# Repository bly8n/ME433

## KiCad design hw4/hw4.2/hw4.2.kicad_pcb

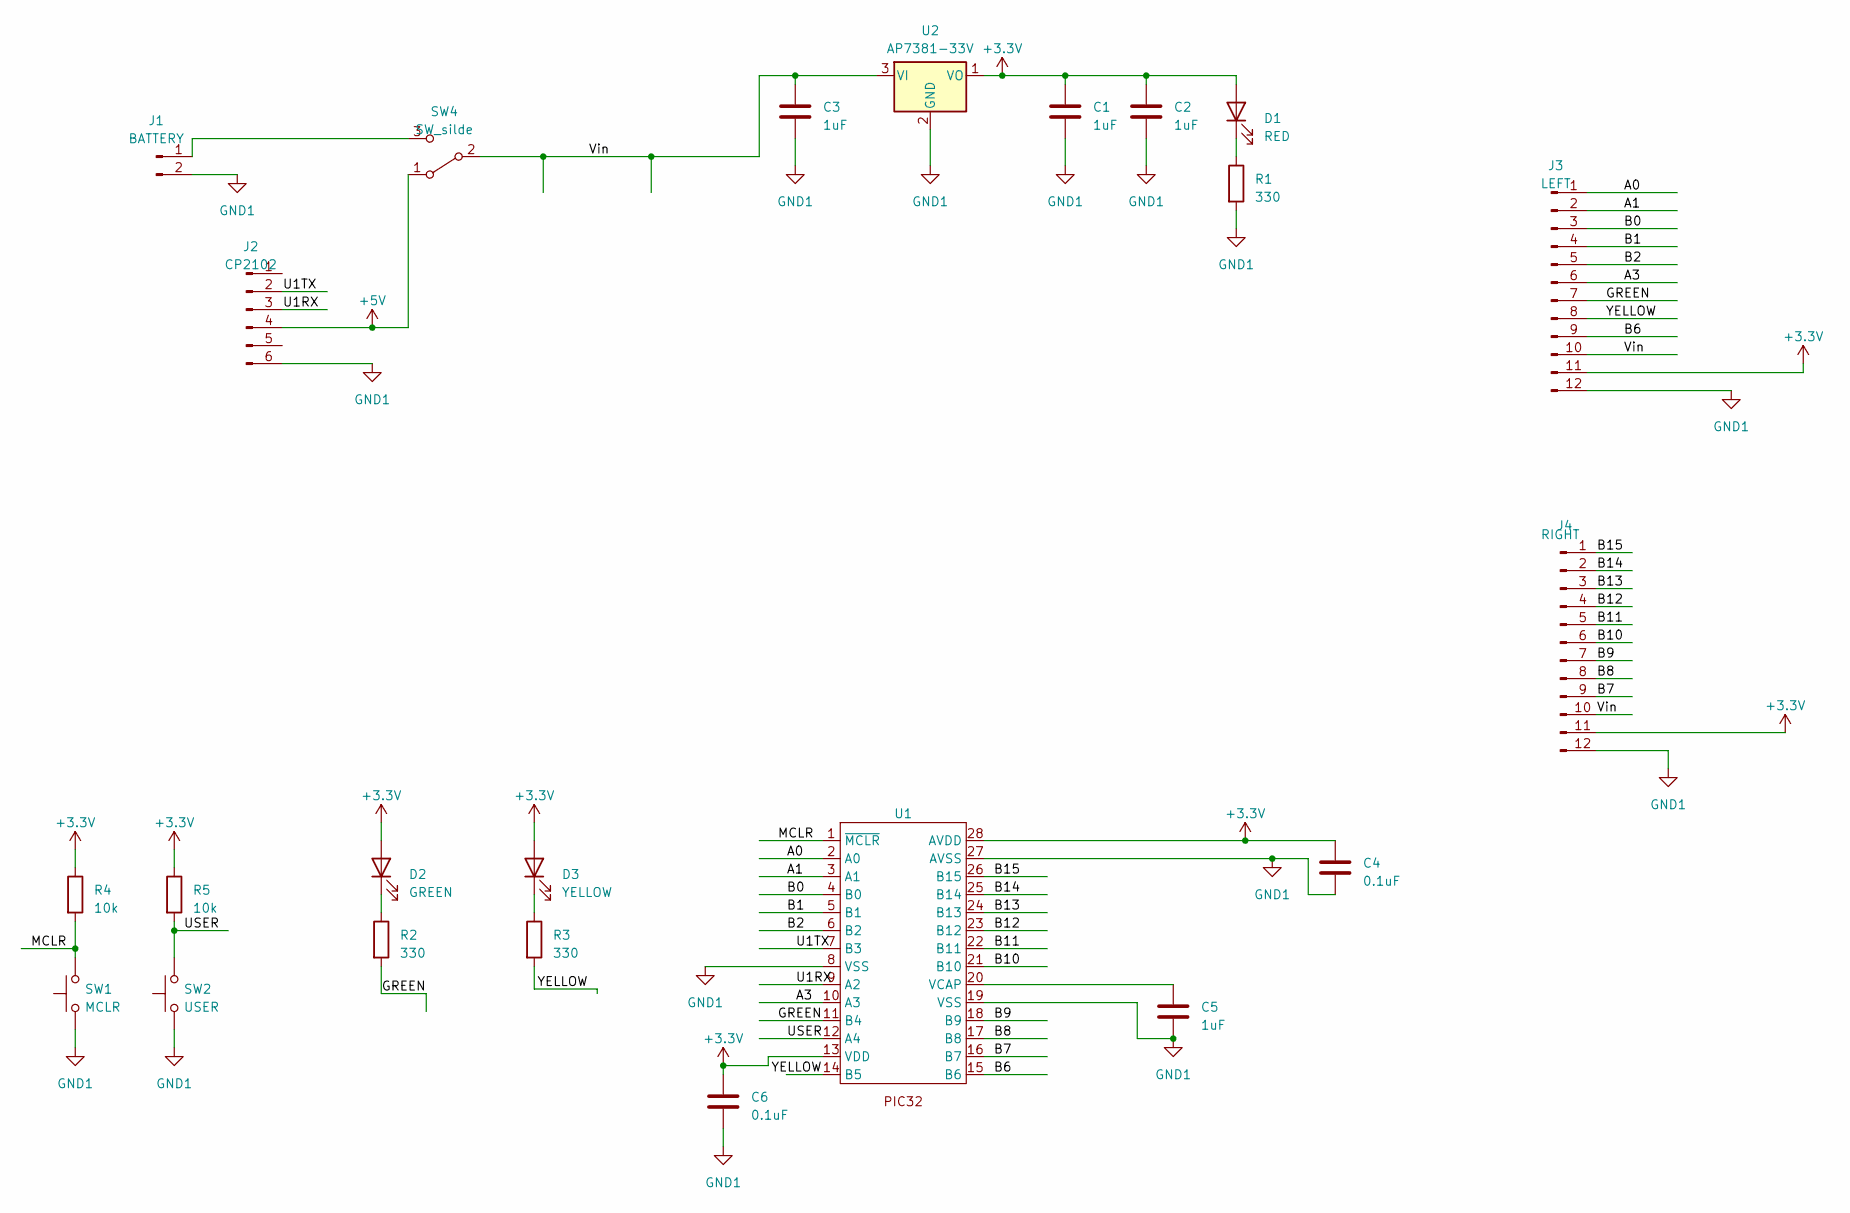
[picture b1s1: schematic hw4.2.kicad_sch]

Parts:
C1, C2, C3, C5: 1uF; C_Disc_D5.1mm_W3.2mm_P5.00mm
C4, C6: 0.1uF; C_Disc_D3.4mm_W2.1mm_P2.50mm
D1: RED; LED_D3.0mm
D2: GREEN; LED_D3.0mm
D3: YELLOW; LED_D3.0mm
J1: BATTERY; PinSocket_1x02_P2.54mm_Vertical
J2: CP2102; PinSocket_1x06_P2.54mm_Vertical
J3: LEFT; PinSocket_1x12_P2.54mm_Vertical
J4: RIGHT; PinSocket_1x12_P2.54mm_Vertical
R1, R2, R3: 330; R_Axial_DIN0207_L6.3mm_D2.5mm_P7.62mm_Horizontal
R4, R5: 10k; R_Axial_DIN0207_L6.3mm_D2.5mm_P7.62mm_Horizontal
SW1: MCLR; pb
SW2: USER; pb
SW4: SW_silde; slidesw2
U1: DIP-28_W7.62mm_Socket
U2: AP7381-33V; TO-92L_Inline

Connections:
+3.3V: C1.1, C2.1, C4.1, C6.1, D1.2 (A), D2.2 (A), D3.2 (A), J3.11, J4.11, R4.1, R5.1, U1.13 (VDD), U1.28 (AVDD), U2.1 (VO)
+5V: J2.4, SW4.1 (A)
/A0: J3.1, U1.2 (A0)
/A1: J3.2, U1.3 (A1)
/A3: J3.6, U1.10 (A3)
/B0: J3.3, U1.4 (B0)
/B1: J3.4, U1.5 (B1)
/B2: J3.5, U1.6 (B2)
/B6: J3.9, U1.15 (B6)
/B7: J4.9, U1.16 (B7)
/B8: J4.8, U1.17 (B8)
/B9: J4.7, U1.18 (B9)
/B10: J4.6, U1.21 (B10)
/B11: J4.5, U1.22 (B11)
/B12: J4.4, U1.23 (B12)
/B13: J4.3, U1.24 (B13)
/B14: J4.2, U1.25 (B14)
/B15: J4.1, U1.26 (B15)
/GREEN: J3.7, R2.2, U1.11 (B4)
/MCLR: R4.2, SW1.2, U1.1 (~MCLR)
/U1RX: J2.3, U1.9 (A2)
/U1TX: J2.2, U1.7 (B3)
/USER: R5.2, SW2.2, U1.12 (A4)
/Vin: C3.1, J3.10, J4.10, SW4.2 (B), U2.3 (VI)
/YELLOW: J3.8, R3.2, U1.14 (B5)
GND1: C1.2, C2.2, C3.2, C4.2, C5.2, C6.2, J1.2, J2.6, J3.12, J4.12, R1.2, SW1.1, SW2.1, U1.8 (VSS), U1.19 (VSS), U1.27 (AVSS), U2.2 (GND)
unnamed: D1.1 (K), R1.1
unnamed: D2.1 (K), R2.1
unnamed: D3.1 (K), R3.1
unnamed: J1.1, SW4.3 (C)
unnamed: C5.1, U1.20 (VCAP)

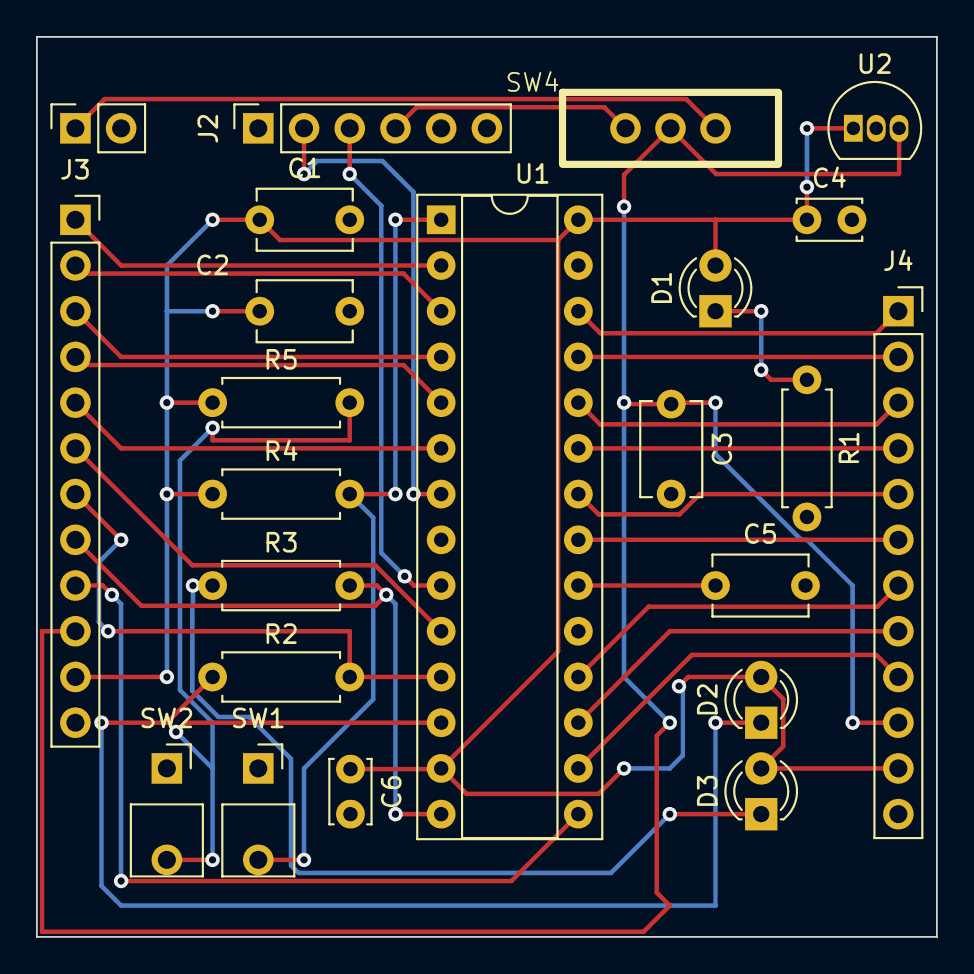
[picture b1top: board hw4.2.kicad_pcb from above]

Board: 2 copper layers, 50.0 x 50.0 mm, 23 parts (0 on the bottom side), 31 nets.

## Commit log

2023-03-28 Starting work on HW1.
2023-04-04 Starting work on HW2.
